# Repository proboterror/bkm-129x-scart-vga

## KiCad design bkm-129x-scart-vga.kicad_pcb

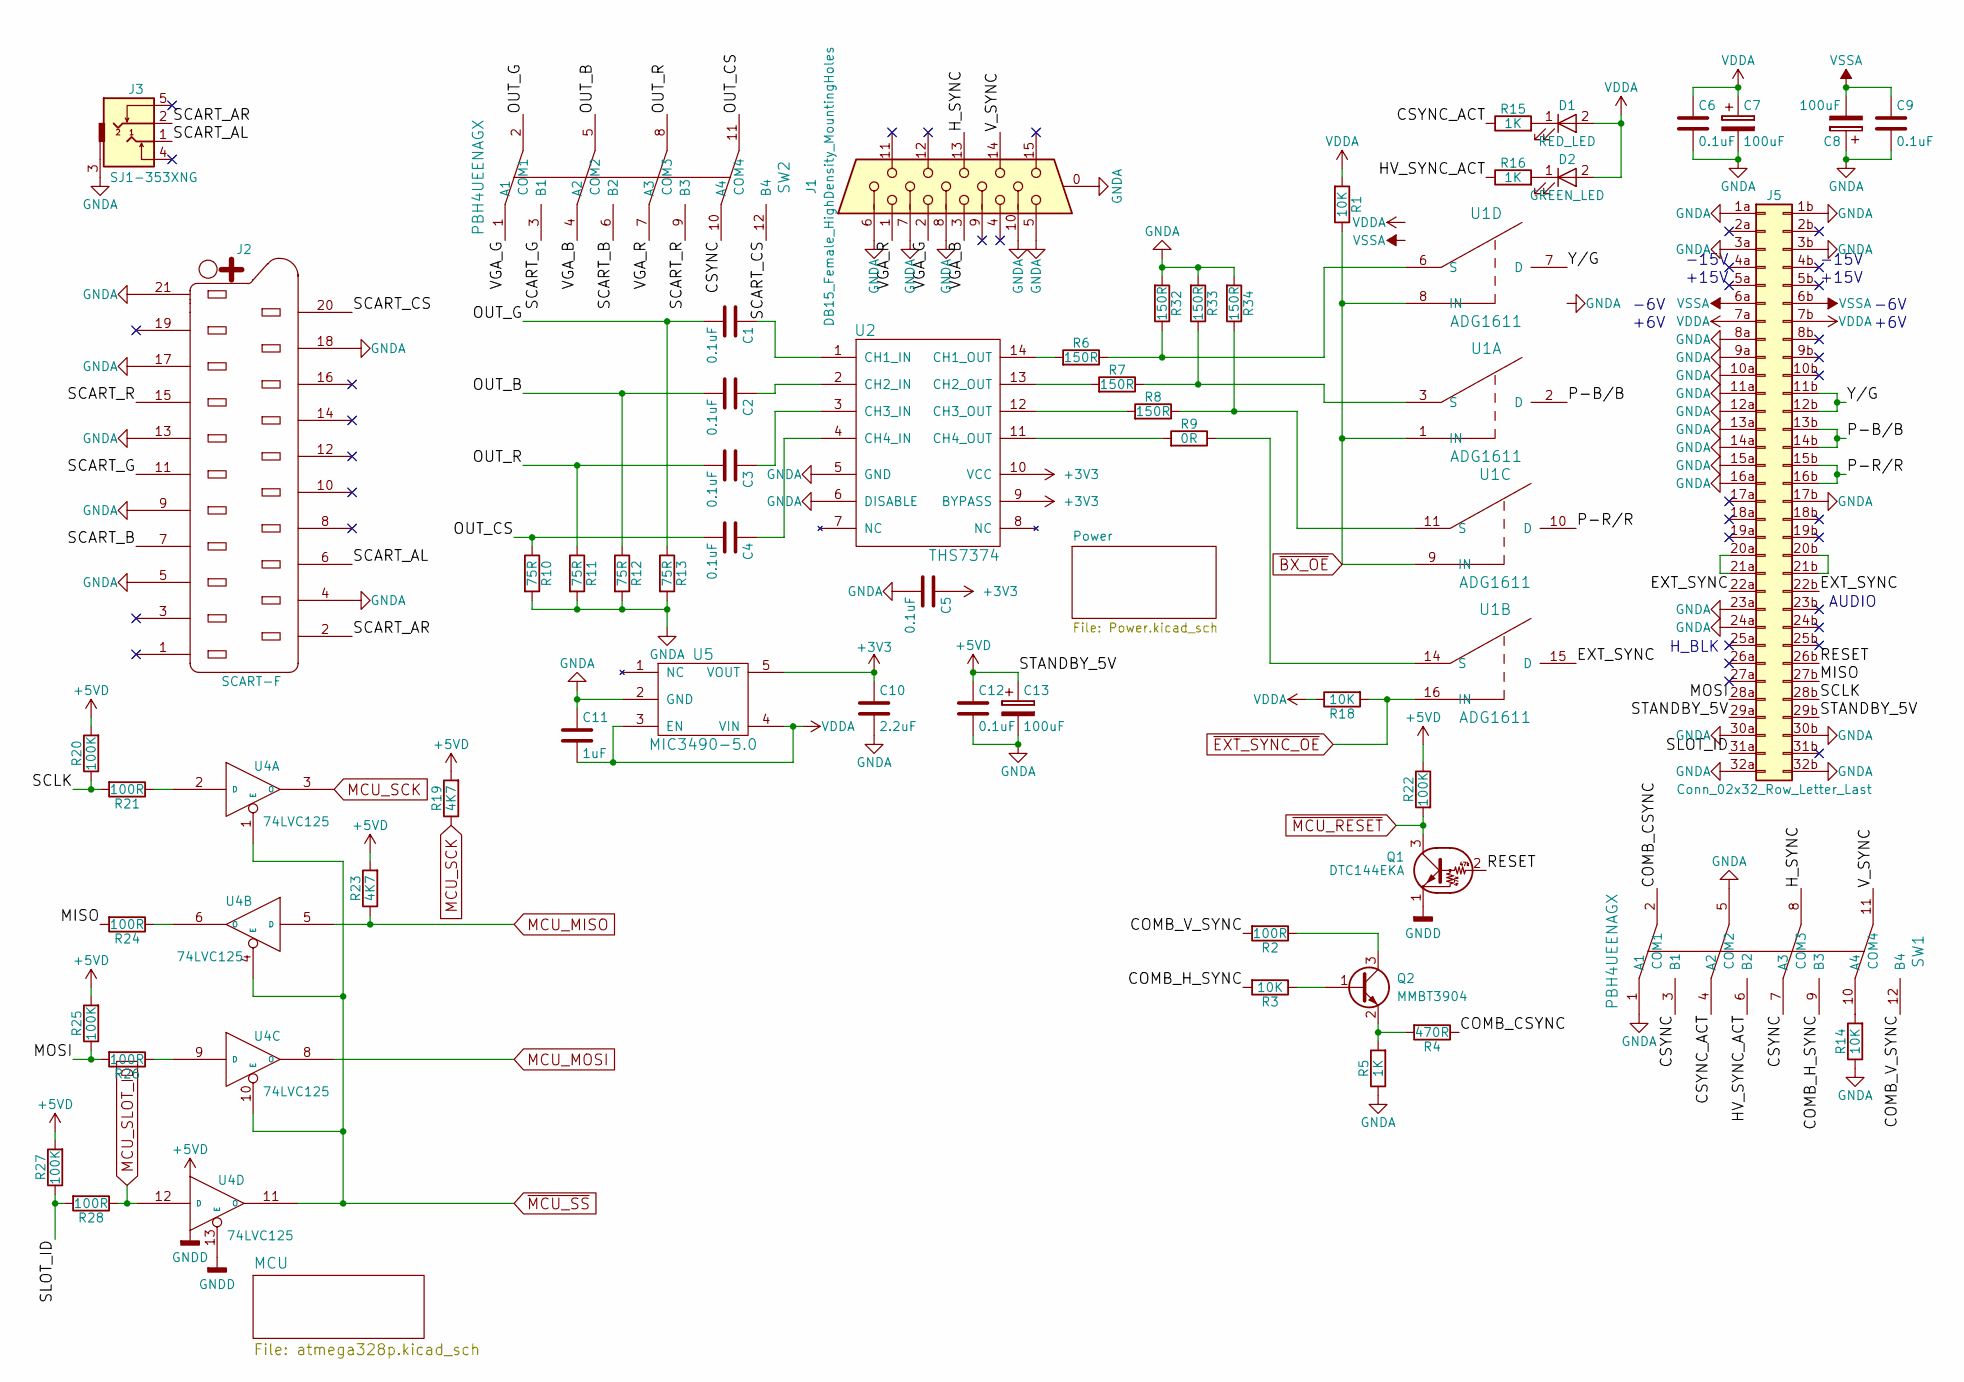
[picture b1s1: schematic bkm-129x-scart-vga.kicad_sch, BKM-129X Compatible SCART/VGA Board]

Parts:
C1, C2, C3, C4, C5, C6, C9, C12: 0.1uF; C_0805_2012Metric_Pad1.18x1.45mm_HandSolder
C7, C8, C13: 100uF; CP_Elec_6.3x5.3
C10: 2.2uF; C_0805_2012Metric_Pad1.18x1.45mm_HandSolder
C11: 1uF; C_0805_2012Metric_Pad1.18x1.45mm_HandSolder
D1: RED_LED; D_0805_2012Metric_Pad1.15x1.40mm_HandSolder
D2: GREEN_LED; D_0805_2012Metric_Pad1.15x1.40mm_HandSolder
J1: DB15_Female_HighDensity_MountingHoles; HD15-VGA
J2: SCART-F; NINIGI-SCART-RA
J3: SJ1-353XNG
J5: Conn_02x32_Row_Letter_Last; STANDARD-PIN-64P-RA
Q1: DTC144EKA; SC-59_Handsoldering
Q2: MMBT3904; SOT-23_Handsoldering
R1, R3, R14, R18: 10K; R_0805_2012Metric_Pad1.20x1.40mm_HandSolder
R2, R21, R24, R26, R28: 100R; R_0805_2012Metric_Pad1.20x1.40mm_HandSolder
R4: 470R; R_0805_2012Metric_Pad1.20x1.40mm_HandSolder
R5, R15, R16: 1K; R_0805_2012Metric_Pad1.20x1.40mm_HandSolder
R6, R7, R8, R32, R33, R34: 150R; R_0805_2012Metric_Pad1.20x1.40mm_HandSolder
R9: 0R; R_0805_2012Metric_Pad1.20x1.40mm_HandSolder
R10, R11, R12, R13: 75R; R_0805_2012Metric_Pad1.20x1.40mm_HandSolder
R19, R23: 4K7; R_0805_2012Metric_Pad1.20x1.40mm_HandSolder
R20, R22, R25, R27: 100K; R_0805_2012Metric_Pad1.20x1.40mm_HandSolder
SW1, SW2: PBH4UEENAGX; PBH4UEE
U1: ADG1611; TSSOP-16_4.4x5mm_P0.65mm
U2: THS7374; TSSOP-14_4.4x5mm_P0.65mm
U4: 74LVC125; SOIC-14_3.9x8.7mm_P1.27mm
U5: MIC3490-5.0; SOT-23-5_HandSoldering

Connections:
+3V3: C5.1, C10.1, U2.9 (BYPASS), U2.10 (VCC), U5.5 (VOUT); also elsewhere on the board
+5VD: C12.1, C13.1, J5.29a, J5.29b, R19.2, R20.2, R22.1, R23.2, R25.2, R27.2, U4.14 (VCC); also elsewhere on the board
/COMB_CSYNC: R4.1, SW1.2 (COM1)
/COMB_H_SYNC: R3.2, SW1.9 (B3)
/COMB_V_SYNC: R2.2, SW1.12 (B4)
/CSYNC: SW1.3 (B1), SW1.7 (A3), SW2.10 (A4)
/CSYNC_ACT: R15.1, SW1.4 (A2)
/EXT_SYNC: J5.22a, J5.22b, U1.15 (D)
/HV_SYNC_ACT: R16.1, SW1.6 (B2)
/H_SYNC: J1.13, SW1.8 (COM3)
/MISO: J5.27b, R24.2
/MOSI: J5.28a, R25.1, R26.2
/OUT_B: C2.2, R12.1, SW2.5 (COM2)
/OUT_CS: C4.2, R10.1, SW2.11 (COM4)
/OUT_G: C1.2, R13.1, SW2.2 (COM1)
/OUT_R: C3.2, R11.1, SW2.8 (COM3)
/P-B/B: J5.13b, J5.14b, U1.2 (D)
/P-R/R: J5.15b, J5.16b, U1.10 (D)
/RESET: J5.26b, Q1.2 (B)
/SCART_AL: J2.6, J3.1
/SCART_AR: J2.2, J3.2
/SCART_B: J2.7, SW2.6 (B2)
/SCART_CS: J2.20, SW2.12 (B4)
/SCART_G: J2.11, SW2.3 (B1)
/SCART_R: J2.15, SW2.9 (B3)
/SCLK: J5.28b, R20.1, R21.2
/SLOT_ID: J5.31a, R27.1, R28.2
/VGA_B: J1.3, SW2.4 (A2)
/VGA_G: J1.2, SW2.1 (A1)
/VGA_R: J1.1, SW2.7 (A3)
/V_SYNC: J1.14, SW1.11 (COM4)
/Y/G: J5.11b, J5.12b, U1.7 (D)
MCU_MISO: R23.1, U4.5 (D); also elsewhere on the board
MCU_MOSI: U4.8 (O); also elsewhere on the board
MCU_SCK: R19.1, U4.3 (O); also elsewhere on the board
MCU_SLOT_ID: R28.1, U4.12 (D); also elsewhere on the board
unnamed: D1.1 (K), R15.2
unnamed: D2.1 (K), R16.2
unnamed: J5.20a, J5.21a
unnamed: J5.20b, J5.21b
unnamed: Q2.1 (B), R3.1
unnamed: Q2.3 (C), R2.1
unnamed: Q2.2 (E), R4.2, R5.2
unnamed: R14.2, SW1.10 (A4)
unnamed: R7.1, R33.1, U1.3 (S)
unnamed: R9.1, U1.14 (S)
unnamed: R8.1, R34.1, U1.11 (S)
unnamed: R6.1, R32.1, U1.6 (S)
unnamed: C1.1, U2.1 (CH1_IN)
unnamed: R6.2, U2.14 (CH1_OUT)
unnamed: C2.1, U2.2 (CH2_IN)
unnamed: R7.2, U2.13 (CH2_OUT)
unnamed: C3.1, U2.3 (CH3_IN)
unnamed: R8.2, U2.12 (CH3_OUT)
unnamed: C4.1, U2.4 (CH4_IN)
unnamed: R9.2, U2.11 (CH4_OUT)
unnamed: R21.1, U4.2 (D)
unnamed: R24.1, U4.6 (O)
unnamed: R26.1, U4.9 (D)
VDDA: C6.1, C7.1, C11.2, D1.2 (A), D2.2 (A), J5.7a, J5.7b, R1.2, R18.1, U1.13 (VDD), U5.3 (EN), U5.4 (VIN); also elsewhere on the board
VSSA: C8.2, C9.1, J5.6a, J5.6b, U1.4 (VSS)
~BX_OE: R1.1, U1.1 (IN), U1.8 (IN), U1.9 (IN); also elsewhere on the board
~EXT_SYNC_OE: R18.2, U1.16 (IN); also elsewhere on the board
~MCU_RESET: Q1.3 (C), R22.2; also elsewhere on the board
~MCU_SS: U4.1 (E), U4.4 (E), U4.10 (E), U4.11 (O); also elsewhere on the board

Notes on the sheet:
+15V
-6V
H_BLK
+6V
AUDIO
-15V

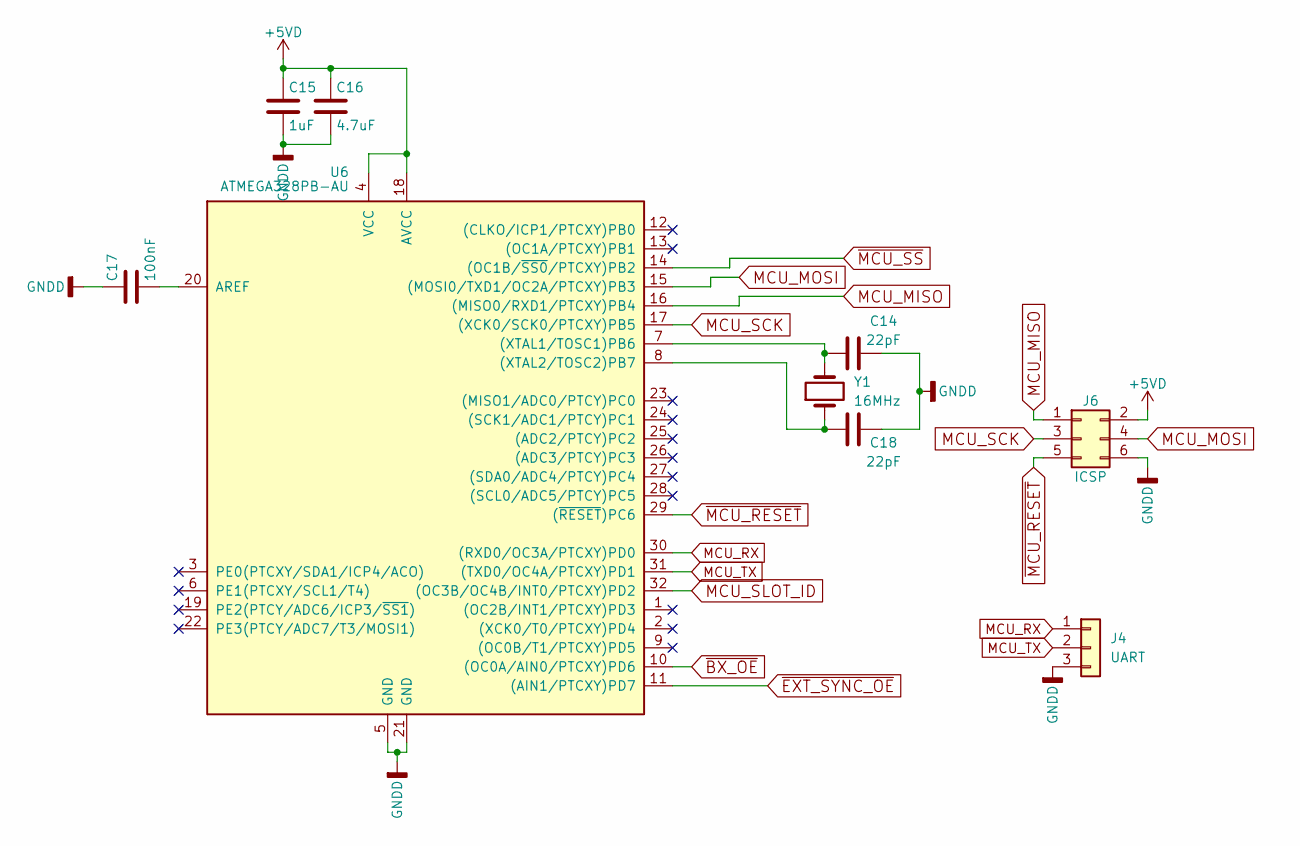
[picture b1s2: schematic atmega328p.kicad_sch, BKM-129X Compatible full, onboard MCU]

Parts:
C14, C18: 22pF; C_0805_2012Metric_Pad1.18x1.45mm_HandSolder
C15: 1uF; C_0805_2012Metric_Pad1.18x1.45mm_HandSolder
C16: 4.7uF; C_0805_2012Metric_Pad1.18x1.45mm_HandSolder
C17: 100nF; C_0805_2012Metric_Pad1.18x1.45mm_HandSolder
J4: UART; PinHeader_1x03_P2.54mm_Vertical
J6: ICSP; Pin_Header_Straight_2x03_Pitch2.54mm
U6: ATMEGA328PB-AU; TQFP-32_7x7mm_P0.8mm
Y1: 16MHz; Crystal_HC49-U_Vertical

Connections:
+5VD: C15.1, C16.1, J6.2, U6.4 (VCC), U6.18 (AVCC); also elsewhere on the board
MCU_MISO: J6.1, U6.16 ((MISO0/RXD1/PTCXY)PB4); also elsewhere on the board
MCU_MOSI: J6.4, U6.15 ((MOSI0/TXD1/OC2A/PTCXY)PB3); also elsewhere on the board
MCU_RX: J4.1, U6.30 ((RXD0/OC3A/PTCXY)PD0)
MCU_SCK: J6.3, U6.17 ((XCK0/SCK0/PTCXY)PB5); also elsewhere on the board
MCU_SLOT_ID: U6.32 ((OC3B/OC4B/INT0/PTCXY)PD2); also elsewhere on the board
MCU_TX: J4.2, U6.31 ((TXD0/OC4A/PTCXY)PD1)
unnamed: C14.1, U6.7 ((XTAL1/TOSC1)PB6), Y1.2
unnamed: C18.1, U6.8 ((XTAL2/TOSC2)PB7), Y1.1
unnamed: C17.2, U6.20 (AREF)
~BX_OE: U6.10 ((OC0A/AIN0/PTCXY)PD6); also elsewhere on the board
~EXT_SYNC_OE: U6.11 ((AIN1/PTCXY)PD7); also elsewhere on the board
~MCU_RESET: J6.5, U6.29 ((~RESET)PC6); also elsewhere on the board
~MCU_SS: U6.14 ((OC1B/~SS0/PTCXY)PB2); also elsewhere on the board

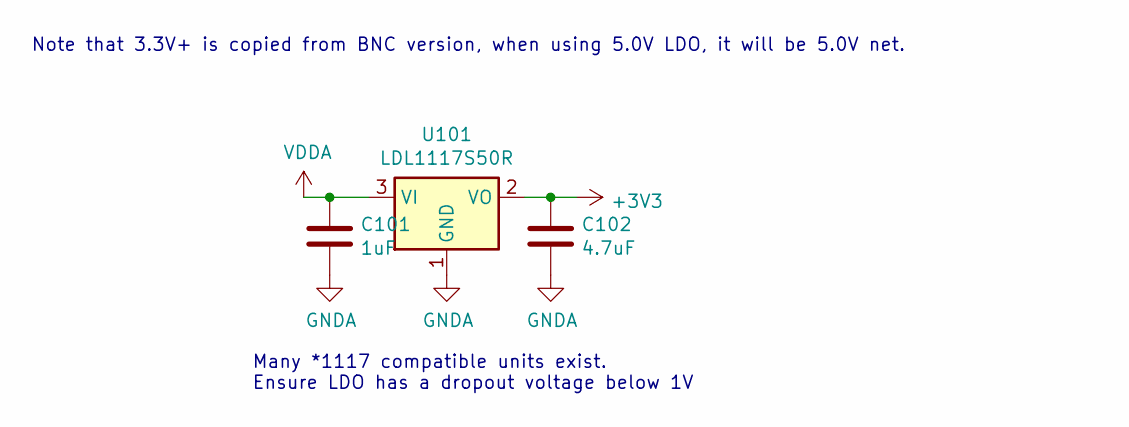
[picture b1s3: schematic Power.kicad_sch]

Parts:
C101: 1uF; C_0805_2012Metric_Pad1.18x1.45mm_HandSolder
C102: 4.7uF; C_0805_2012Metric_Pad1.18x1.45mm_HandSolder
U101: LDL1117S50R; SOT-223-3_TabPin2

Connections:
+3V3: C102.1, U101.2 (VO); also elsewhere on the board
VDDA: C101.1, U101.3 (VI); also elsewhere on the board

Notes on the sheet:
Note that 3.3V+ is copied from BNC version, when using 5.0V LDO, it will be 5.0V net.
Many *1117 compatible units exist. Ensure LDO has a dropout voltage below 1V

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
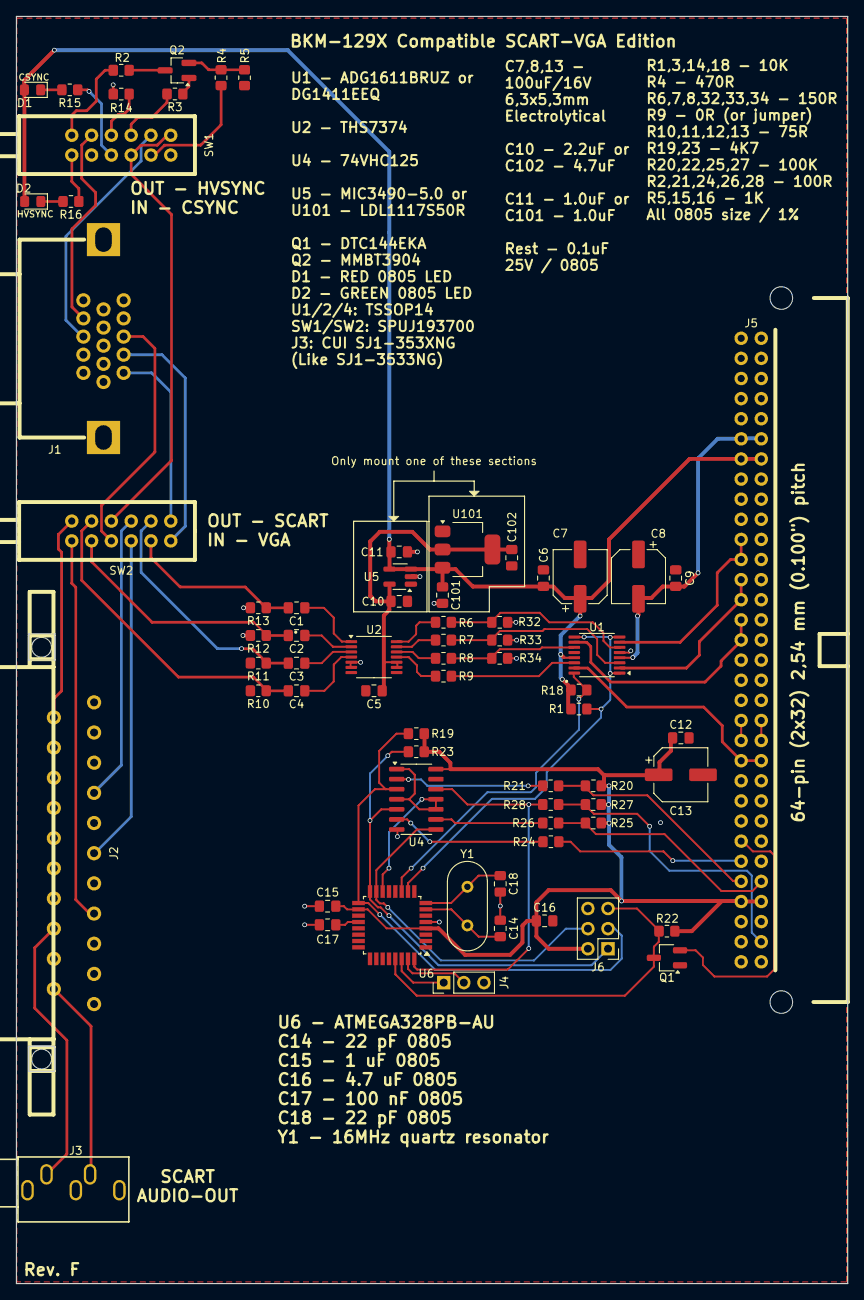
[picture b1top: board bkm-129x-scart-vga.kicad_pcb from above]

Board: 2 copper layers, 105.0 x 160.0 mm, 69 parts (0 on the bottom side), 71 nets.

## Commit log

2025-01-08 Convert to KiCad 8.0.
2025-01-08 Edit J1 VGA DB15: Move X -0.7775 mm Edit footprint silkscreen matching board edge Change mounting holes to: Pad shape: Rectangular 4.2 x 4.2, Hole shape: Oval 3.2 x 2.2.
    Unfill all zones.
2025-01-09 Edit SW1, SW2: Move X 0.4 mm Remove mounting holes
2025-01-09 Remove U3 Arduino Nano from PCB and schematic.
2025-01-09 Replace CSTNE16M0VH3L000R0 ceramic resonator with HC49S quartz crystal and capacitors.
2025-01-09 Update PCB from schematic, arrange MCU components on PCB.
2025-01-09 Add debug UART connector to schematic and PCB. Edit silkscreen MCU description.
2025-01-10 Add J5 DIN41612_B_2x32_Male_Horizontal_THT mounting holes with 2 mm clearance.
2025-01-10 Edit SW1, SW2 footprint: move silkscreen drawing: X: -0.45
2025-01-10 Add github link to PCB silkscreen.
2025-01-10 Change C14, C18 footprints from 1206 to 0805.
2025-01-10 Change U4 footprint to TSSOP-14 (74LVC125AD.112).
2025-01-10 Update PCB silkscreen description.
2025-01-11 PCB: change input analog RGBS tracks width from 0.25 to 0.35 mm.
2025-01-11 PCB: fix DRC warnings: update footprints.
2025-01-11 * PCB: change output analog RGBS tracks width from 0.25 to 0.35 mm.
2025-03-08 Edit PCB silkscreen BOM description: 74VHC125 not 74LVC125 See comment https://www.reddit.com/r/crtgaming/comments/f5u1zo/bkm129x_cheapedition/ 74LVC125AD112 (NXP/Nexperia) is not compatible. Tested 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
